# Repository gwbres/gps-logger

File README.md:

## Mini GPS data logger

The idea behind this project is to have a
long lasting GPS data logger.

The selected module is the PMTK3339 GPS receiver
provided by Adafruits on a breakout board.

An MSP430 is used to kick start the GPS module,
this device has extensive options to reduce power
consumption.

### What you can learn from this project

* How to compile code for MSP430 devices
* Use MSP430 features to reduce power consumption
* 
* Manipulate coordinates
	* D° M' S"
	* Decimal degrees
	* etc.. 
* Discover NMEA data 

### User interface

</img>

[Use the project Wiki to learn how to use the GUI & the API](https://github.com/gwbres/gps-logger/wiki)

### Getting started

Required packages:

```bash
# apt-get install binutils-msp430 gcc-msp430 msp430-libc mspdebug
```

compile the program with

```bash
make
```

I use *mspdebug* and an MSP430 launchpad to program my MCUs:

```bash
# mspdebug rf2500
# erase
# prog main.hex
# run
```

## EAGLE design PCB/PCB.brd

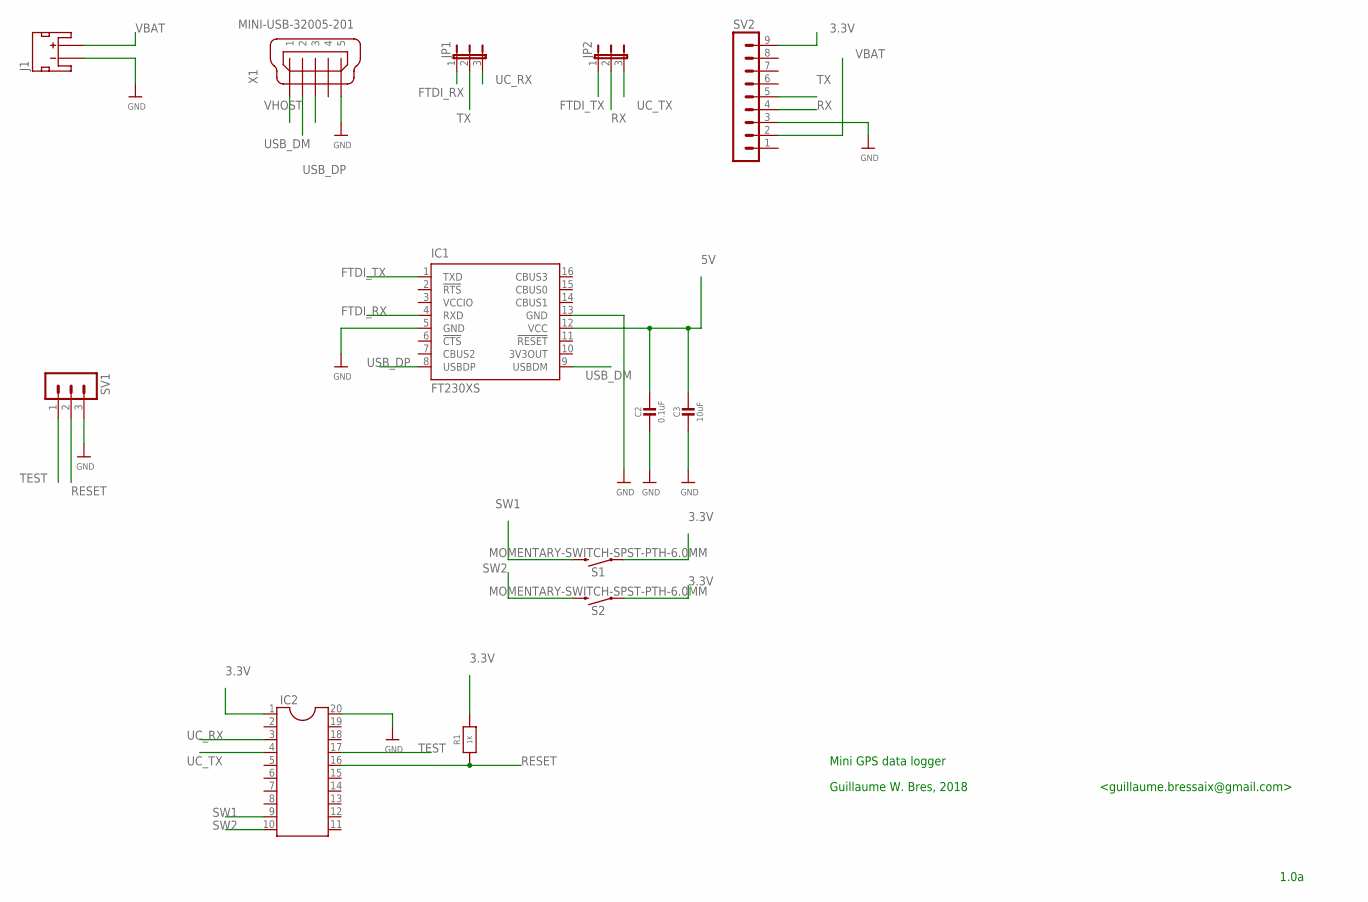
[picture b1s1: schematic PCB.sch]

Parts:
C2: 0.1uF; 0805-NO
C3: 10uF; 0805-NO
IC1: FT230XS; SSOP16
IC2: DIL20
J1: JST_2MM_MALE; JST-2-SMD
JP1, JP2: JP2E; JP2
R1: 1K; 0805-NO
S1, S2: MOMENTARY-SWITCH-SPST-PTH-6.0MM; TACTILE_SWITCH_PTH_6.0MM
SV1: MA03-1
SV2: MA09-1
X1: MINI-USB-32005-201; 32005-201

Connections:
3.3V: IC2.1, R1.2, S1.1, S2.1, SV2.9
5V: C2.1, C3.1, IC1.12 (VCC)
FTDI_RX: IC1.4 (RXD), JP1.1
FTDI_TX: IC1.1 (TXD), JP2.1
GND: C2.2, C3.2, IC1.5 (GND), IC1.13 (GND), IC2.20, J1.1 (-), SV1.3, SV2.3, X1.5
RESET: IC2.16, R1.1, SV1.2
RX: JP2.2, SV2.4
SW1: IC2.9, S1.3 (2)
SW2: IC2.10, S2.3 (2)
TEST: IC2.17, SV1.1
TX: JP1.2, SV2.5
UC_RX: IC2.3, JP1.3
UC_TX: IC2.4, JP2.3
USB_DM: IC1.9 (USBDM), X1.2
USB_DP: IC1.8 (USBDP), X1.3
VBAT: J1.2 (+), SV2.2
VCCIO: IC1.3 (VCCIO)
VHOST: X1.1

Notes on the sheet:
Guillaume W. Bres, 2018
Mini GPS data logger
1.0a
<guillaume.bressaix@gmail.com>

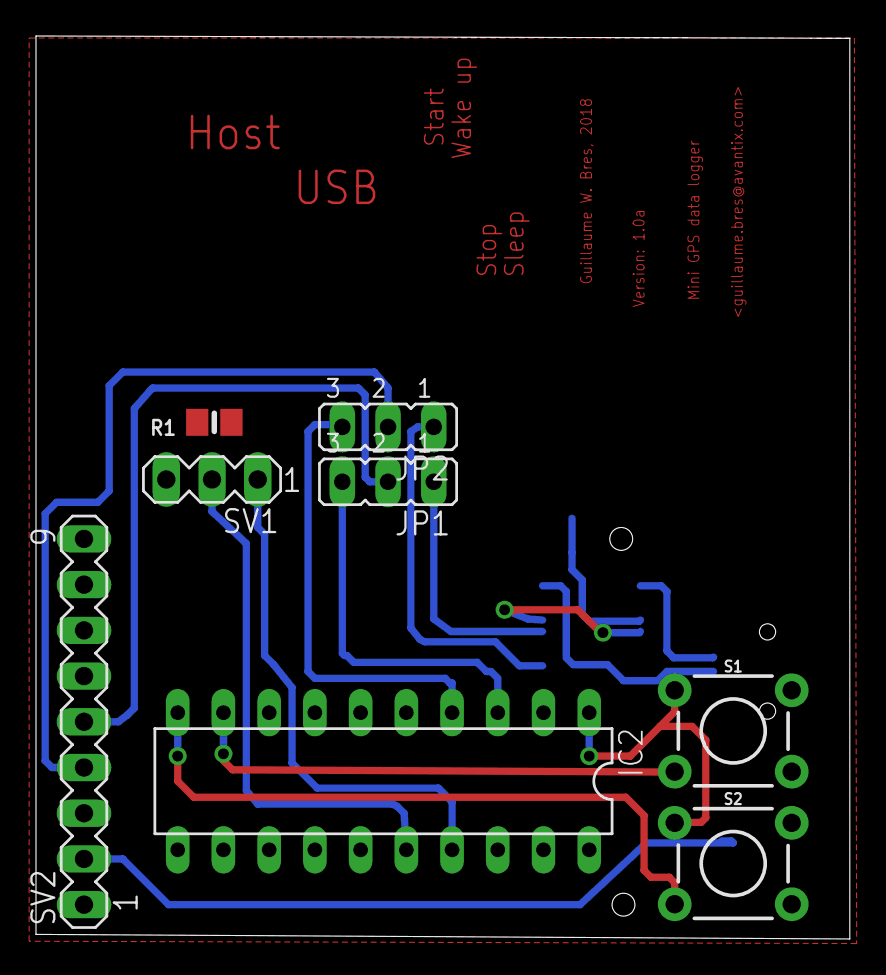
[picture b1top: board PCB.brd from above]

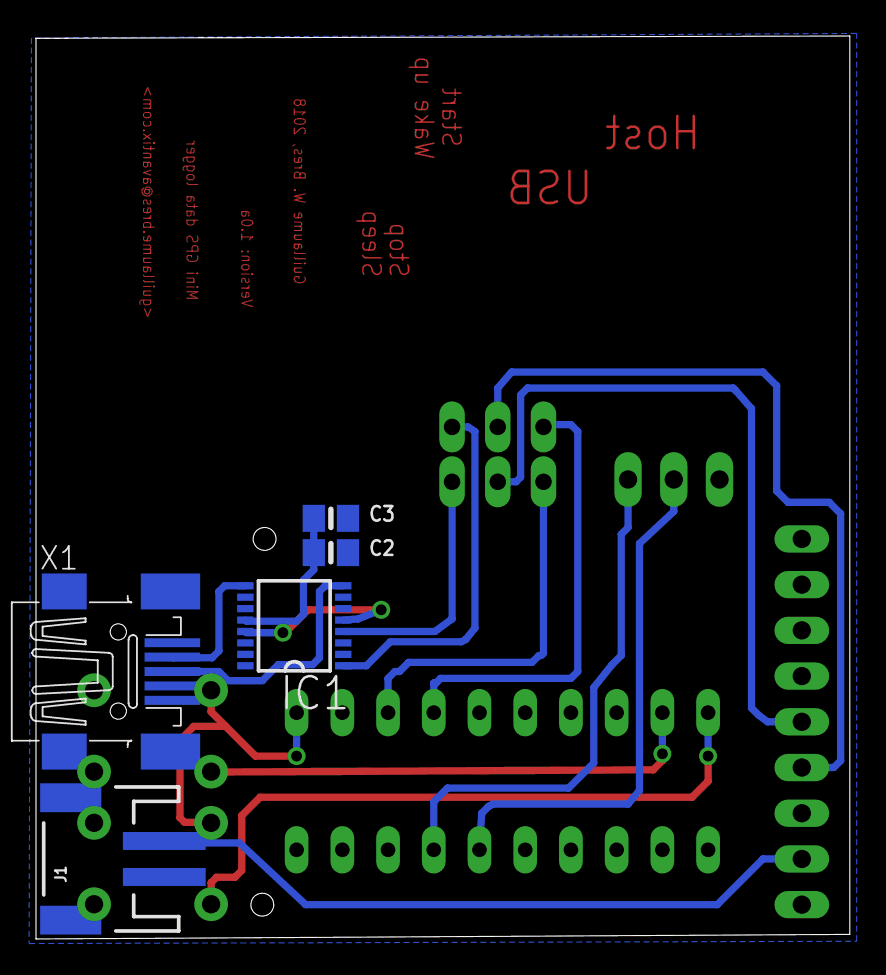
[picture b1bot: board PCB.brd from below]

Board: 2 copper layers, 45.2 x 50.2 mm, 13 parts (5 on the bottom side), 16 nets.

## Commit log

2018-04-14 added main.c: IRQ/GPIO example & associated makefile
2018-04-14 created gitignore
2018-04-14 created README file
2018-04-15 added UART initialization + hello world
2018-04-15 added TX done logic
2018-04-21 renamed MSP/toolchain dir, introduced LOWPOWER mode
2018-04-21 introduced lowpower mode; finalized UART demo; working on PIE: GPIO interrupt
2018-04-21 added python tool to use the PMTK module directly
2018-04-21 do not track .nmea & .kml data files
2018-04-21 introduced GPS/PMTK module lib. & associated test method
2018-04-21 improved help() a little bit
2018-04-21 removed empty line
2018-04-22 working on NMEA/KML/GPX tool suite; improved CLI
2018-04-22 do not track .gpx files
2018-04-23 improved file operations
2018-04-23 working on LOWPOWER option
2018-04-23 fixed NMEA->KML and NMEA->GPX conversions
2018-04-24 created seperated method to parse all waypoints in .nmea file
2018-04-24 working on first solution to view waypoints
2018-04-25 fixed degree to D,M,S converion, fixed nmea->kml & nmea->gpx conversion, introduced geoplotlib to visualize waypoints
2018-04-25 updated python dependencies
2018-04-25 added time stamps as labels in coordinates viewer
2018-04-25 increase default point size
2018-04-25 fixed serial.open problem: class constructor already does the job
2018-04-26 working on USB/serial interface
2018-04-26 added CLI interface to python toolbox
2018-04-26 added a few mentions on file format
2018-04-26 removed non needed comment
2018-04-26 improved waypoints parsing
2018-04-26 corrected python toolbox CLI
2018-04-27 removed commented out stuff
2018-04-30 improved status query/display
2018-04-30 corrected DUMP_FLASH command
2018-04-30 modified approach: parse waypoints / introduced locus parsing / erase is OK / logging is OK / status too but must be improved
2018-05-02 working on locus parser
2018-05-02 modified header
2018-05-02 added 3 GPIO ISRs
2018-05-02 added first debouncer scheme
2018-05-02 introduced status logic & added status LED
2018-05-03 removed unneeded commands; some will never be used in embedded context; introduced stand-by/wake-up
2018-05-03 removed test method; introduced stand-by/wake-up
2018-05-03 added API_Q_FIX_CTRL, improved serial port CLI, working on locus data parsing
2018-05-03 added control over locus logging rate
2018-05-03 corrected wakeup() method
2018-05-03 working on module interactions / should wait until complete answer has been received but it is faulty at the moment
2018-05-03 removed deprecated function
2018-05-03 LPM0 mode seems to be working but requires more in depth tests
2018-05-04 added kml->waypoints parser; working on flash dump
2018-05-12 modified command line interface; added elevation profile viewer
2018-05-12 elevation profile is now plotted against accumuated distance using Haversine formula
2018-05-12 corrected x axis
2018-05-12 updated CLI
2018-05-13 added PCB 1.0
2018-05-13 added board 1.0: still WIP
2018-05-13 hide eagle/board routing related files
2018-05-13 moved software suite to subdir
2018-05-13 moved PMTK & GPS functionnalities to seperate files/objects
2018-05-13 added PMTK functionnalities
2018-05-13 created Waypoint object
2018-05-13 added GPS Track object
2018-05-13 upated readme: added first tests
2018-05-13 added PCB section
2018-05-14 use checksum to check line content, faulty coordinates will now raise an error
2018-05-14 corrected file name
2018-05-14 verify checksum: raise error when faulty
2018-05-14 catch error: do not append waypoint to GPS Track when checksum is faulty. This naturally discards faulty caracters in log files
2018-05-14 added method to create waypoint from PMTK/locus log: -- still WIP -- 3 bytes left out in parsing method
2018-05-14 added constructor from a locus log file
2018-05-14 added Date method: will later be used when plotting
2018-05-14 added PCB 1.0 (still WIP)
2018-05-14 added PCB picture
2018-05-14 modified PCB1.0
2018-05-14 use built in zero padding function
2018-05-14 removed non needed shebang
2018-05-15 added string conversion method for GPSTrack object
2018-05-15 added TotalDistance method, used in drawOnMap method for x axis
2018-05-16 Checksum is now a class method to be called outside
2018-05-16 added & validated constructor from locus log
2018-05-16 added Track constructore from locus log: parsing is made here because locus/log may contain N records; only appends valid coordinates
2018-05-16 improved _str_ cast
2018-05-16 added locus/log tool suite
2018-05-16 improved date/utc handling: build data object from either UTC or UTC+date
2018-05-16 introduced new timeDiff method
2018-05-16 introduced new average speed method
2018-05-16 elevation profile is now a seperate function
2018-05-16 added new instant. speed method
2018-05-16 elevation profile is now drawn in seperate method
2018-05-17 moved elevation profile to seperate function; introduced drawOnMap(qMap)
2018-05-17 corrected instantSpeed()
2018-05-17 created GUI using Qt5/PyQtGraph & QMap
2018-05-17 created new method: accumulatedDistance()
2018-05-17 do not track locus log files
2018-05-17 added list methods
2018-05-17 removed deprecated geoplot lib. replaced by qMap
2018-05-17 added date in native constructor
2018-05-17 map is now properly centered, single marker on last waypoint
2018-05-18 included new object PMTK & defined window dimensions
2018-05-18 defined & coded all previous methods to talk the GPS module
2018-05-18 add a marker every 10 waypoints (should be improved): requires qMap patch
2018-05-18 removed deprecated script: replaced by console/command line interface
2018-05-18 corrected status & sendCommand()
2018-05-18 removed track viewer
2018-05-18 introduced getWaypoints()
2018-05-18 append all gps tracks in case several were selected
2018-05-18 GPIOs have changed, introduced LPM0 mode
2018-05-18 working on new method: FLASH usage, to determine amount of records stored
2018-05-18 introduced OBJCOPY & flash method
2018-05-18 introduced LPM3 mode
2018-05-18 make targets have changed
2018-05-18 added python related stuff
2018-05-18 removed symbol
2018-05-19 moved most important stuff to wiki page
2018-05-19 added GUI1 test
2018-05-19 added screenshot
2018-05-19 reduced picture size
2018-05-19 added link to wiki page
2018-05-19 added proto board 1.0
2018-05-19 corrected link syntax
2018-05-19 added new method: search by date
2018-05-19 added missing format
2018-05-19 introduced QListWidget to control Track visualization
2018-05-19 draw all waypoints otherwise it's confusing
2018-05-19 introduced navigation through GPS track
2018-05-19 added _eq_ operator: equal if GPS coordinates are strictly identical
2018-05-19 created new method: search waypoint within self
2018-05-19 introduced onMarkerClicks
2018-05-19 use counter for default waypoint markers identification: will be used to remove them later on
2018-05-19 introduced clear() method
2018-05-20 init_uart: 9600 b/s
2018-05-20 introduced new methods: Highest/Lowest point: use them to add special markers
2018-05-21 averageSpeed: between two given indexes
2018-05-21 stacked plots together, introduced 'rm' functionnality
2018-05-21 moved from a QListWidget to a QTreeWidgetItem: better sorting options, multiple selection possible
2018-05-21 modified _str_ cast to be used in QTreeWidget
2018-05-21 introduced QTree/MultipleSelection & related highlight event: need to work on deleteMarkers logic
2018-05-21 corrected distance calculation: requires coordinates in decimal degrees
2018-05-21 updated gui images
2018-05-21 updated & resized gui image
2018-05-21 corrected image link syntax
2018-05-21 v1.0 almost done
2018-05-23 updated header

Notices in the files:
parts and their libraries:
SparkFun-Connectors: Licensing: Creative Commons ShareAlike 4.0 International - https://creativecommons.org/licenses/by-sa/4.0
